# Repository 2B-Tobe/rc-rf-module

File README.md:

# RC RF Module

A 2.4 GHz multi-protocol RC transmitter module and receiver on one board, built around the EFR32MG24
(RF-BM-MG24B2I module), with an optional second radio — an SX1278 (RA-01) — that carries the same channels
on 459 MHz beside the 2.4 GHz link. One firmware serves both roles and both board variants.

| | |
|---|---|
| **Transmitter module** | takes the channels from a transmitter's encoder — PPM, or Multiprotocol serial frames — and sends them on nRF24, RLINK, FrSky D8, FrSky D16 (ACCST v1/v2, EU-LBT or FCC) or DSMX, with the 459 MHz link beside it when the RA-01 is fitted |
| **Receiver** | 8 servo outputs, PPM and SBUS; with the RA-01 fitted it listens on both bands and takes the servos from 459 MHz when 2.4 GHz goes quiet |
| **Setup** | protocol jumpers, or a setup stored in the module: written over its serial pins with the hand-held **Controller** (this repository) or a terminal |
| **Links of its own** | RLINK (two-way 2.4 GHz with telemetry, adaptive channels and power, alarms), nRF24 (the original 11 ms link), UK 459 MHz (10-byte hopping link) |

## Two board variants, one firmware

- **2.4 GHz only** — the RA-01 and its parts are left off. The firmware notices (`no SX1278 answered`) and runs
  2.4 GHz only.
- **2.4 GHz + 459 MHz** — the RA-01 fitted. The firmware runs the 459 MHz link beside every transmitter
  mode (selectable Single / Dual) and the 459 MHz receiver beside every receiver mode.

The servo outputs are on the same pins for both variants (`firmware/servo_pins.h`).

## What is where

| Folder | |
|---|---|
| `firmware/` | the EFR32 project (Simplicity SDK 2026.6.1, RAIL), `build.ps1`, `cfg.ps1`, prebuilt hex files — see `firmware/README.md` |
| `controller/` | the RF Module Controller: an STM32F103C8 box with a 128×64 display that sets the module up over its serial pins — STM32CubeIDE project, manual |
| `hardware/rf_module/` | the module carrier board: KiCad project, Gerbers, BOM and placement files |
| `hardware/controller/` | the controller board: KiCad project, Gerbers, BOM and placement files |
| `docs/` | operating quick sheet, flashing with an ST-Link, the serial input and setup command reference, the RLINK description |
| `CREDITS.md` | people, projects and components this builds on, with their licences |

## Start here

1. **Build a board** — `hardware/rf_module/README.md` (what to order, what to leave off for the 2.4 GHz-only variant).
2. **Flash it** — with only an ST-Link: `docs/FLASHING_STLINK.md` (the prebuilt firmware and a setup file for each
   role, no USB-serial adapter needed); to build it yourself: `firmware/README.md`.
3. **Use it** — `docs/QUICK_SHEET_EFR32_Module.md`: connections, roles, modes, bind, failsafe, LEDs.
4. **Feed it** — `docs/SERIAL_INPUT.md`: what a transmitter has to send (PPM or the Multiprotocol serial frame),
   and the text commands any programmer can use to set the module up.
5. **Controller** — `controller/README.md` and `controller/docs/MANUAL.md` to build and use the setup box.

## Regulatory note

The 2.4 GHz side is built for EU use: DSMX at 22 ms only and 18 dBm, FrSky D16 EU-LBT (Sub 0/1) with listen-before-talk (the D16 FCC versions, Sub 2/3/5, are for receivers with FCC firmware and have none), RLINK
with a clear-channel check before every packet. The 459 MHz link uses the UK 458.5–459.5 MHz model-control
band at 100 mW; check what your country allows before fitting the RA-01.

## Licence

The firmware, the documentation and the hardware design files are released under the **GNU GPL v3** (see
`LICENSE`). The Controller (`controller/`) is under the **MIT licence** (`controller/LICENSE`). Third-party
components keep their own licences, listed in `CREDITS.md`. The Silicon Labs RAIL radio library (a binary under Zlib)
and two printf files under the Silicon Labs MSLA are **not** in this repository: they come with the Simplicity SDK,
and `build.ps1` copies them in. The firmware licence includes an additional permission to build it with that library (top of `LICENSE`).

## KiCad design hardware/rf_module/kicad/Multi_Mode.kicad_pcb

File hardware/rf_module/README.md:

# RF module carrier board (Multi_Mode)

Carrier for the RF-BM-MG24B2I (EFR32MG24) module with the header for the RA-01 (SX1278, 459 MHz) radio.
Both board variants are this one PCB:

| Variant | Fit | Leave off |
|---|---|---|
| 2.4 GHz only | everything except the RA-01 | the RA-01 and its reset capacitor |
| 2.4 GHz + 459 MHz | everything | — |

The firmware is the same for both; it detects the RA-01 at power-up.

## Files

| | |
|---|---|
| `Multi_Mode.pdf` | the schematic |
| `kicad/` | the KiCad project (KiCad 5 format: `.pro`, `.sch`, `.kicad_pcb`; KiCad 6 and later open and convert it). The EFR32 module's symbol comes from the project library `rf_star`; its footprint is embedded in the board file |
| `gerber/` | Gerber and drill files (4 layers), and the same as one zip for the board house |
| `bom/` | `Multi_Mode-top-pos.csv` — component placement, top side |

## Connections (EFR32 pins)

| Function | Pin |
|---|---|
| J3 serial: RX in / TX out, GND | PA06 / PA05 (3.3 V, 1 k in series on RX) |
| PPM in, and telemetry out (to the encoder, or EdgeTX bay pin 5) | PB01, through the Schottky diode D3 (see below) |
| BIND, RANGE, F/S (jumpers / buttons to GND) | PB00, PB02, PB03 |
| Protocol jumpers PC00, PC01, PC02 | to GND |
| LED_A, LED_B | PC04, PC05 |
| Buzzer (passive) | PD02 |
| Receiver servo outputs 1–8 | PA07 PB04 PD04 PD05 PA00 PA08 PA09 PB05 |
| Receiver PPM out, SBUS out | PC03 (270 Ω series), PA03 |
| Receiver battery sense (47 k / 10 k divider, 100 nF) | PA04 |
| RA-01: SCK, MISO, MOSI, NSS, RESET | PC06, PC07, PC08, PC09, PD03 (DIO pins unconnected) |
| SWD (flashing) | SWCLK, SWDIO, GND, 3.3 V |

Supply: 3.3 V LDO on board; mind its heat above ~8 V input with both radios sending.

## The PPM line and D3

PB01 started as a PPM input only. The Schottky diode D3 between the PPM connector and PB01 (net PPM_IN) suits
that: the outside can pull the line low, the module never drives it. Since then the same line also carries
telemetry **out** of the module, to the MiTo encoder and to bay pin 5 (S.Port) of an EdgeTX radio. D3 blocks that
direction, so the radio sees no status, no protocol list and no sensors (a black-and-white radio then cannot even
reach the MiTo protocol).

- **Boards built so far:** on a transmitter module, bridge D3 with a solder blob or a short wire. A receiver does
  not use this line and needs nothing.
- **Next revision:** a 1 k resistor in parallel with D3. PPM still comes in through the diode, telemetry goes out
  through the resistor, and no bridge is needed.

The line keeps its TVS diode either way. The MiTo encoder and EdgeTX radios drive it at 3.3 V; with a radio that
drives 5 V, the 1 k (rather than a plain bridge) also limits the current into the EFR32 pin.

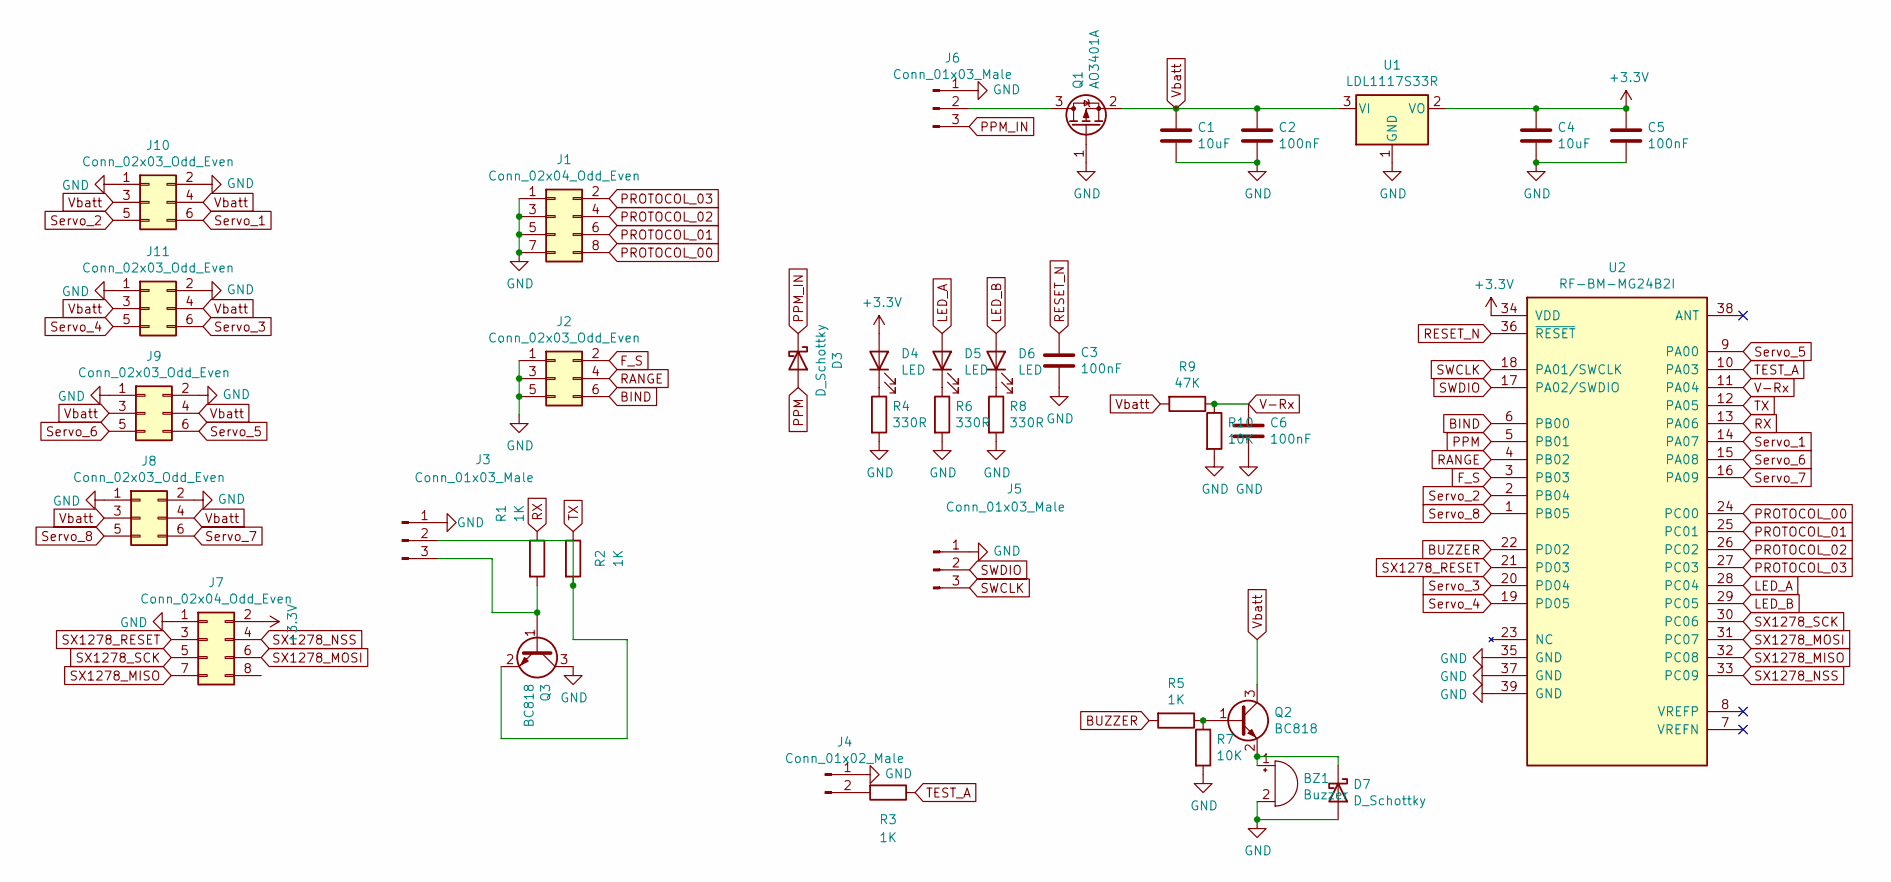
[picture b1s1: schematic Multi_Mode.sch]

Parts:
BZ1: Buzzer; CUI_CSS-0578-SMT
C1, C4: 10uF; C_0805_2012Metric
C2, C3, C5, C6: 100nF; C_0603_1608Metric
D3, D7: D_Schottky; D_SOD-323
D4, D5, D6: LED; LED_0603_1608Metric
J1, J7: Conn_02x04_Odd_Even; PinHeader_2x04_P2.54mm_Vertical
J2, J8, J9, J10, J11: Conn_02x03_Odd_Even; PinHeader_2x03_P2.54mm_Vertical
J3, J5, J6: Conn_01x03_Male; PinHeader_1x03_P2.54mm_Vertical
J4: Conn_01x02_Male; PinHeader_1x02_P2.54mm_Vertical
Q1: AO3401A; SOT-23
Q2, Q3: BC818; SOT-23
R1, R2, R3, R5: 1K; R_0603_1608Metric
R4, R6, R8: 330R; R_0603_1608Metric
R7, R10: 10K; R_0603_1608Metric
R9: 47K; R_0603_1608Metric
U1: LDL1117S33R; SOT-223-3_TabPin2
U2: RF-BM-MG24B2I

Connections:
+3V3: C4.1, C5.1, D4.2 (A), J7.2, U1.2 (VO), U2.34 (VDD)
BIND: J2.6, U2.6 (PB00)
BUZZER: R5.2, U2.22 (PD02)
F_S: J2.2, U2.3 (PB03)
GND: BZ1.2 (+), C1.2, C2.2, C3.2, C4.2, C5.2, C6.2, D7.2 (A), J1.1, J1.3, J1.5, J1.7, J2.1, J2.3, J2.5, J3.1, J4.1, J5.1, J6.1, J7.1, J8.1, J8.2, J9.1, J9.2, J10.1, J10.2, J11.1, J11.2, Q1.1 (G), Q3.3 (C), R4.2, R6.2, R7.2, R8.2, R10.2, U1.1 (GND), U2.35 (GND), U2.37 (GND), U2.39 (GND)
LED_A: D5.2 (A), U2.28 (PC04)
LED_B: D6.2 (A), U2.29 (PC05)
unnamed: BZ1.1 (-), D7.1 (K), Q2.2 (E)
unnamed: D4.1 (K), R4.1
unnamed: D5.1 (K), R6.1
unnamed: D6.1 (K), R8.1
unnamed: J3.2, Q3.2 (E), R2.2
unnamed: J3.3, Q3.1 (B), R1.2
unnamed: J4.2, R3.2
unnamed: J6.2, Q1.3 (D)
unnamed: Q2.1 (B), R5.1, R7.1
PPM: D3.2 (A), U2.5 (PB01)
PPM_IN: D3.1 (K), J6.3
PROTOCOL_00: J1.8, U2.24 (PC00)
PROTOCOL_01: J1.6, U2.25 (PC01)
PROTOCOL_02: J1.4, U2.26 (PC02)
PROTOCOL_03: J1.2, U2.27 (PC03)
RANGE: J2.4, U2.4 (PB02)
RESET_N: C3.1, U2.36 (~RESET)
RX: R1.1, U2.13 (PA06)
SWCLK: J5.3, U2.18 (PA01/SWCLK)
SWDIO: J5.2, U2.17 (PA02/SWDIO)
SX1278_MISO: J7.7, U2.32 (PC08)
SX1278_MOSI: J7.6, U2.31 (PC07)
SX1278_NSS: J7.4, U2.33 (PC09)
SX1278_RESET: J7.3, U2.21 (PD03)
SX1278_SCK: J7.5, U2.30 (PC06)
Servo_1: J10.6, U2.14 (PA07)
Servo_2: J10.5, U2.2 (PB04)
Servo_3: J11.6, U2.20 (PD04)
Servo_4: J11.5, U2.19 (PD05)
Servo_5: J9.6, U2.9 (PA00)
Servo_6: J9.5, U2.15 (PA08)
Servo_7: J8.6, U2.16 (PA09)
Servo_8: J8.5, U2.1 (PB05)
TEST_A: R3.1, U2.10 (PA03)
TX: R2.1, U2.12 (PA05)
V-Rx: C6.1, R9.1, R10.1, U2.11 (PA04)
Vbatt: C1.1, C2.1, J8.3, J8.4, J9.3, J9.4, J10.3, J10.4, J11.3, J11.4, Q1.2 (S), Q2.3 (C), R9.2, U1.3 (VI)

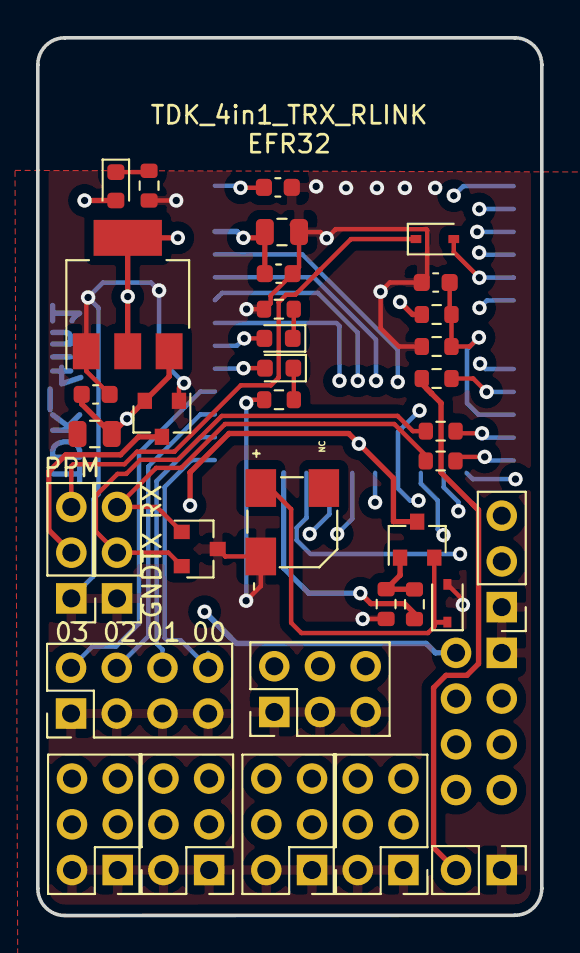
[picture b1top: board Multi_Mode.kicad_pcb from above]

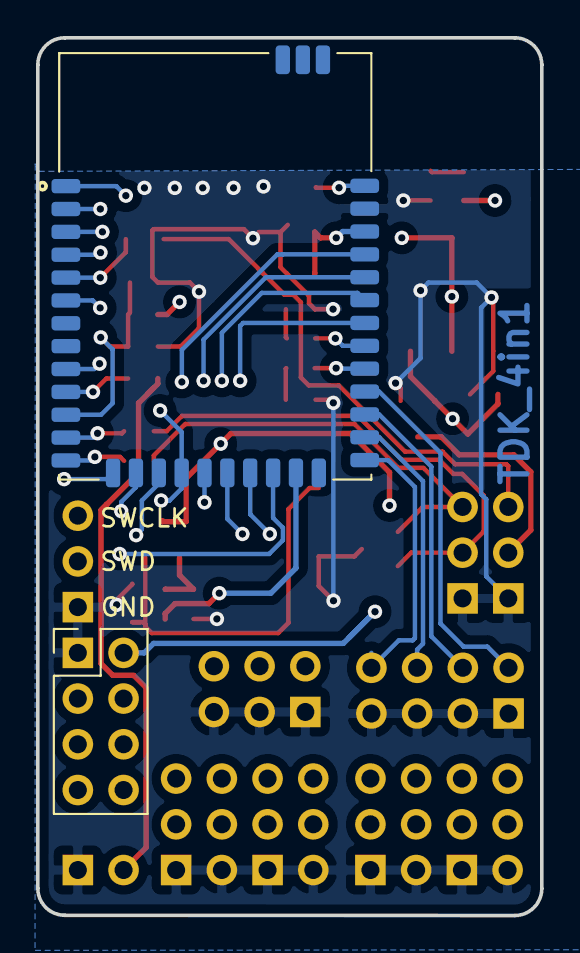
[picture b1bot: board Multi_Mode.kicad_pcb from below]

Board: 4 copper layers, 28.0 x 48.8 mm, 38 parts (2 on the bottom side), 44 nets.

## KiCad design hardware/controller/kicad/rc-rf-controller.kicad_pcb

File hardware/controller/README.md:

# Controller board (rc-rf-controller)

The hand-held box: STM32F103C8, a 128×64 UC1701 SPI display (JLX12864), five keys, buzzer, two 3-pin leads
to the module and an SWD header. Four-layer board.

## Files

| | |
|---|---|
| `rc-rf-controller.pdf` | the schematic |
| `kicad/` | the KiCad project (KiCad 5 format; KiCad 6 and later open and convert it). The tactile switch symbol is in the project library `rc-rf-controller-parts`; everything else is from KiCad's standard libraries; footprints are embedded in the board file |
| `gerber/` | Gerber and drill files, and the same as one zip for the board house |
| `bom/` | `rc-rf-controller-top-pos.csv` — component placement, top side |

## Connections (STM32 pins, see `controller/Core/Inc/board.h`)

| Function | Pin |
|---|---|
| Display SPI2: SCK, MOSI, CD/A0, RST, backlight | PB13, PB15, PB14, PB12, PB2 |
| Keys to GND: INC, DEC, BACK, ENTER, AUX | PB4, PA10, PB11, PB3, PB8 |
| To the module: J3 RX | PA9 (USART1 TX) |
| From the module: J3 TX | PA8 (software receiver; alternatives PA10, PA3 — `Core/Inc/serial.h`) |
| SWD | SWCLK PA14, SWDIO PA13, GND, 3.3 V |

Supply 3.3 V on board. The module's J3 pins are 3.3 V logic as well; GND common.

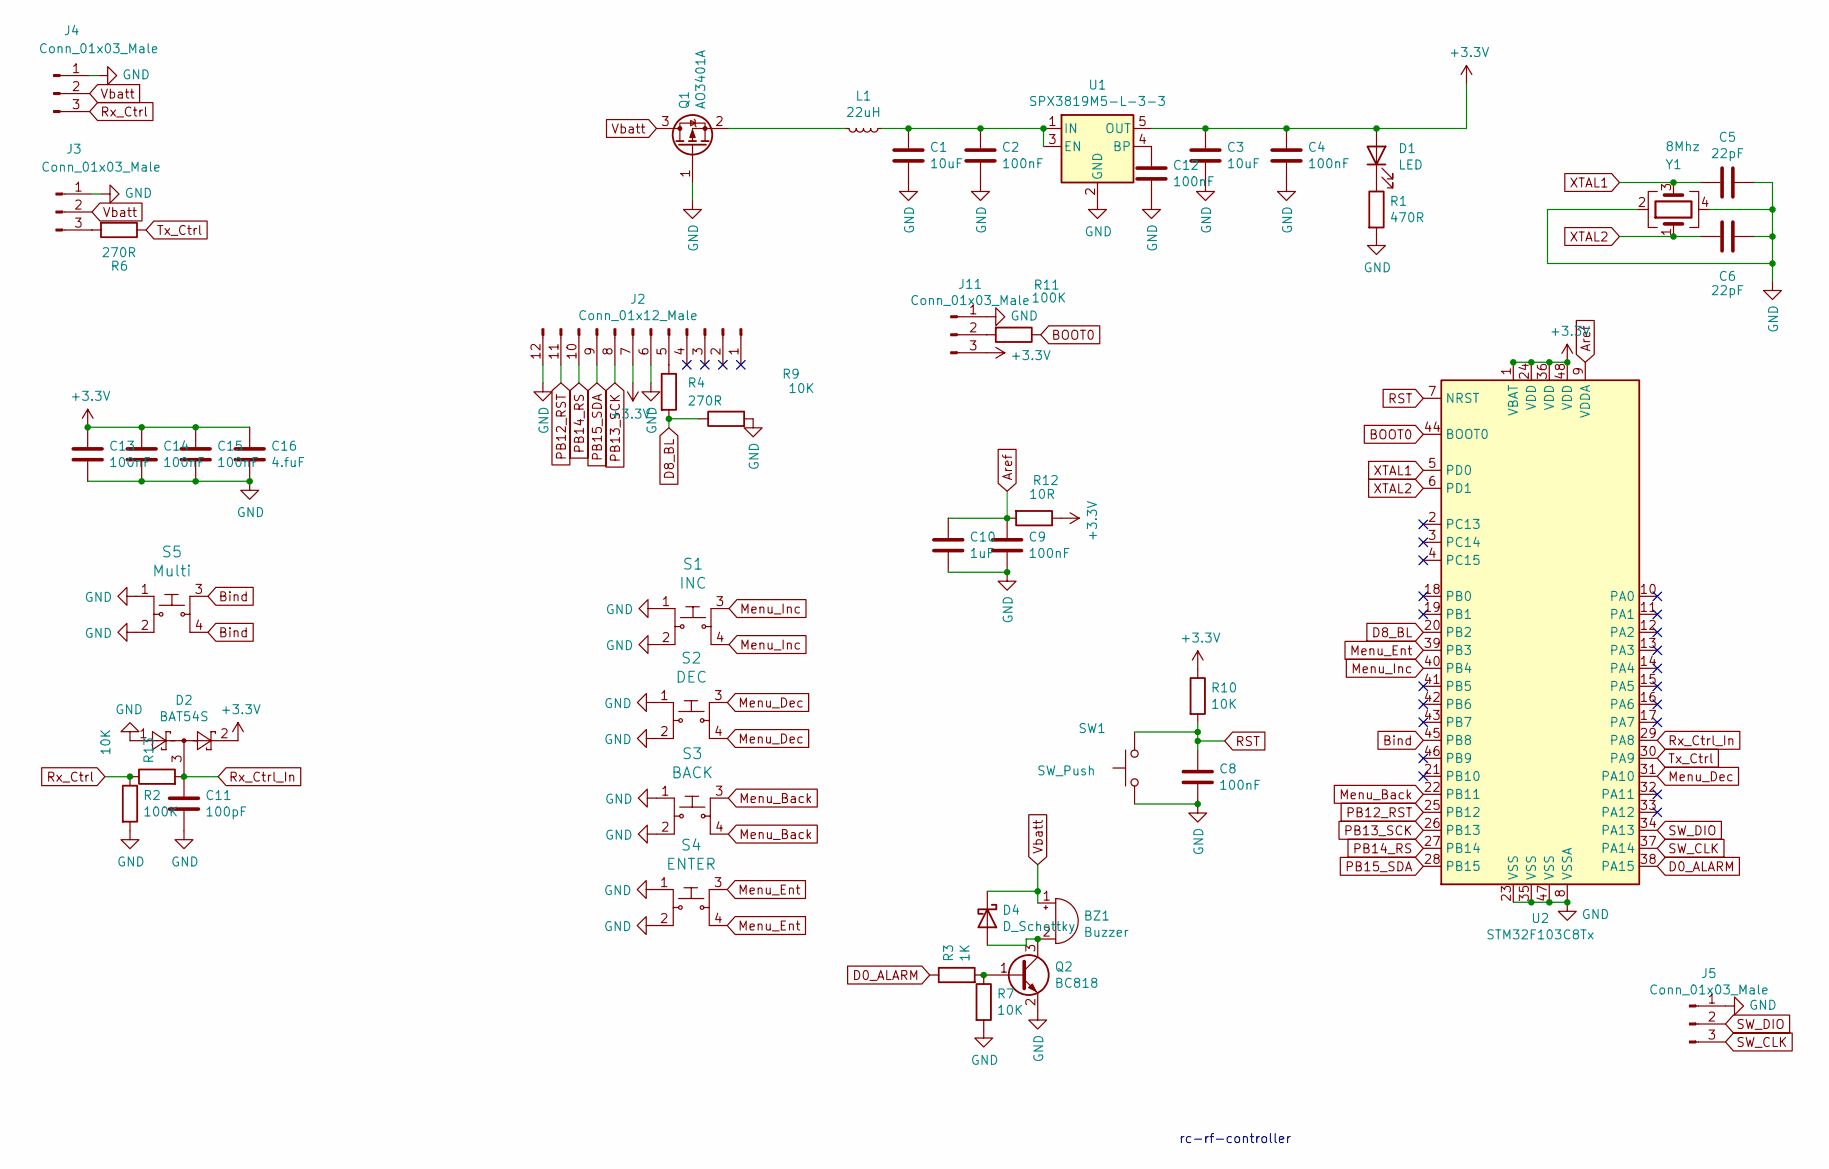
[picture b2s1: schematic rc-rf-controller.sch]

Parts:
BZ1: Buzzer; CUI_CSS-0578-SMT
C1, C3: 10uF; C_0805_2012Metric
C2, C4, C8, C9, C12, C13, C14, C15: 100nF; C_0603_1608Metric
C5, C6: 22pF; C_0603_1608Metric
C10: 1uF; C_0603_1608Metric
C11: 100pF; C_0603_1608Metric
C16: 4.fuF; C_0603_1608Metric
D1: LED; LED_0603_1608Metric
D2: BAT54S; SOT-23
D4: D_Schottky; D_SOD-323
J2: Conn_01x12_Male; PinHeader_1x12_P2.54mm_Vertical
J3, J4, J5: Conn_01x03_Male; PinHeader_1x03_P2.54mm_Vertical
J11: Conn_01x03_Male; SolderJumper-3_P1.3mm_Open_Pad1.0x1.5mm
L1: 22uH; Inductor_6060_MK
Q1: AO3401A; SOT-23
Q2: BC818; SOT-23
R1: 470R; R_0603_1608Metric
R2, R11: 100K; R_0603_1608Metric
R3: 1K; R_0603_1608Metric
R4, R6: 270R; R_0603_1608Metric
R7, R9, R10, R13: 10K; R_0603_1608Metric
R12: 10R; R_0603_1608Metric
S1: INC; SW_1825910-7; MPN 1825910-6; Digi-Key_PN 450-1650-ND
S2: DEC; SW_1825910-7; MPN 1825910-6; Digi-Key_PN 450-1650-ND
S3: BACK; SW_1825910-7; MPN 1825910-6; Digi-Key_PN 450-1650-ND
S4: ENTER; SW_1825910-7; MPN 1825910-6; Digi-Key_PN 450-1650-ND
S5: Multi; SW_1825910-7; MPN 1825910-6; Digi-Key_PN 450-1650-ND
SW1: SW_Push; SW_SPST_B3U-1000P
U1: SPX3819M5-L-3-3; SOT-23-5
U2: STM32F103C8Tx; LQFP-48_7x7mm_P0.5mm
Y1: 8Mhz; Crystal_SMD_3225-4Pin_3.2x2.5mm

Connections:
+3V3: C3.1, C4.1, C13.1, C14.1, C15.1, C16.1, D1.2 (A), D2.2, J2.7, J11.3, R10.1, R12.1, U1.5 (OUT), U2.1 (VBAT), U2.24 (VDD), U2.36 (VDD), U2.48 (VDD)
Aref: C9.1, C10.1, R12.2, U2.9 (VDDA)
BOOT0: R11.1, U2.44 (BOOT0)
Bind: S5.3, S5.4, U2.45 (PB8)
D0_ALARM: R3.1, U2.38 (PA15)
D8_BL: R4.2, R9.1, U2.20 (PB2)
GND: C1.2, C2.2, C3.2, C4.2, C5.1, C6.1, C8.2, C9.2, C10.2, C11.2, C12.2, C13.2, C14.2, C15.2, C16.2, D2.1, J2.6, J2.12, J3.1, J4.1, J5.1, J11.1, Q1.1 (G), Q2.2 (E), R1.2, R2.2, R7.2, R9.2, S1.1, S1.2, S2.1, S2.2, S3.1, S3.2, S4.1, S4.2, S5.1, S5.2, SW1.1, U1.2 (GND), U2.8 (VSSA), U2.23 (VSS), U2.35 (VSS), U2.47 (VSS), Y1.2, Y1.4
Menu_Back: S3.3, S3.4, U2.22 (PB11)
Menu_Dec: S2.3, S2.4, U2.31 (PA10)
Menu_Ent: S4.3, S4.4, U2.39 (PB3)
Menu_Inc: S1.3, S1.4, U2.40 (PB4)
unnamed: BZ1.2 (+), D4.2 (A), Q2.3 (C)
unnamed: C1.1, C2.1, L1.1, U1.1 (IN), U1.3 (EN)
unnamed: C12.1, U1.4 (BP)
unnamed: D1.1 (K), R1.1
unnamed: J2.5, R4.1
unnamed: J3.3, R6.2
unnamed: J11.2, R11.2
unnamed: L1.2, Q1.2 (S)
unnamed: Q2.1 (B), R3.2, R7.1
PB12_RST: J2.11, U2.25 (PB12)
PB13_SCK: J2.8, U2.26 (PB13)
PB14_RS: J2.10, U2.27 (PB14)
PB15_SDA: J2.9, U2.28 (PB15)
RST: C8.1, R10.2, SW1.2, U2.7 (NRST)
Rx_Ctrl: J4.3, R2.1, R13.1
Rx_Ctrl_In: C11.1, D2.3, R13.2, U2.29 (PA8)
SW_CLK: J5.3, U2.37 (PA14)
SW_DIO: J5.2, U2.34 (PA13)
Tx_Ctrl: R6.1, U2.30 (PA9)
Vbatt: BZ1.1 (-), D4.1 (K), J3.2, J4.2, Q1.3 (D)
XTAL1: C5.2, U2.5 (PD0), Y1.3
XTAL2: C6.2, U2.6 (PD1), Y1.1

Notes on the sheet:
rc-rf-controller

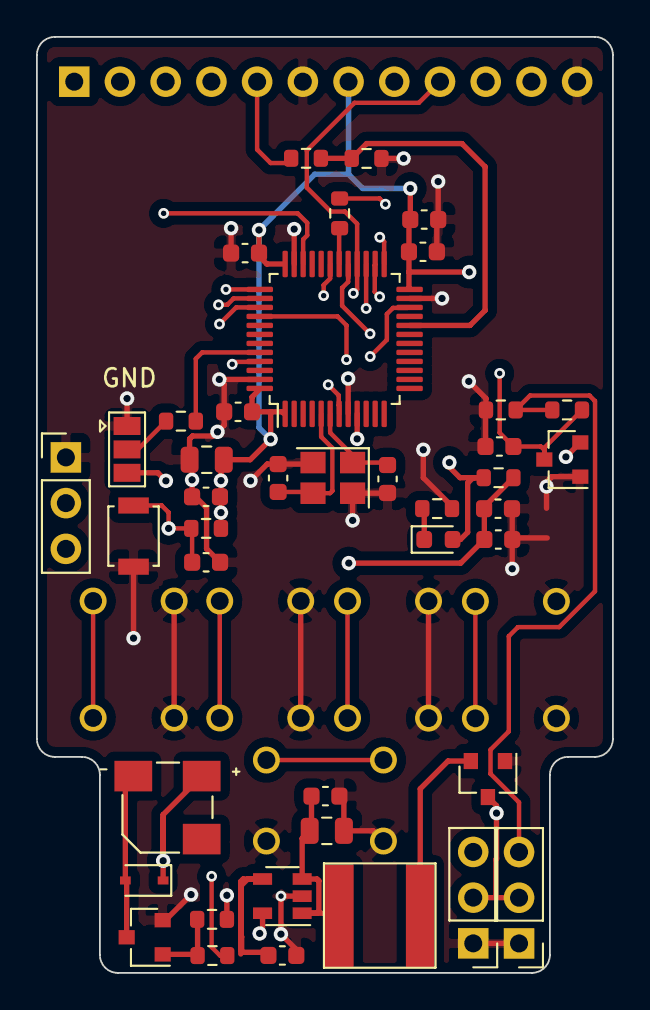
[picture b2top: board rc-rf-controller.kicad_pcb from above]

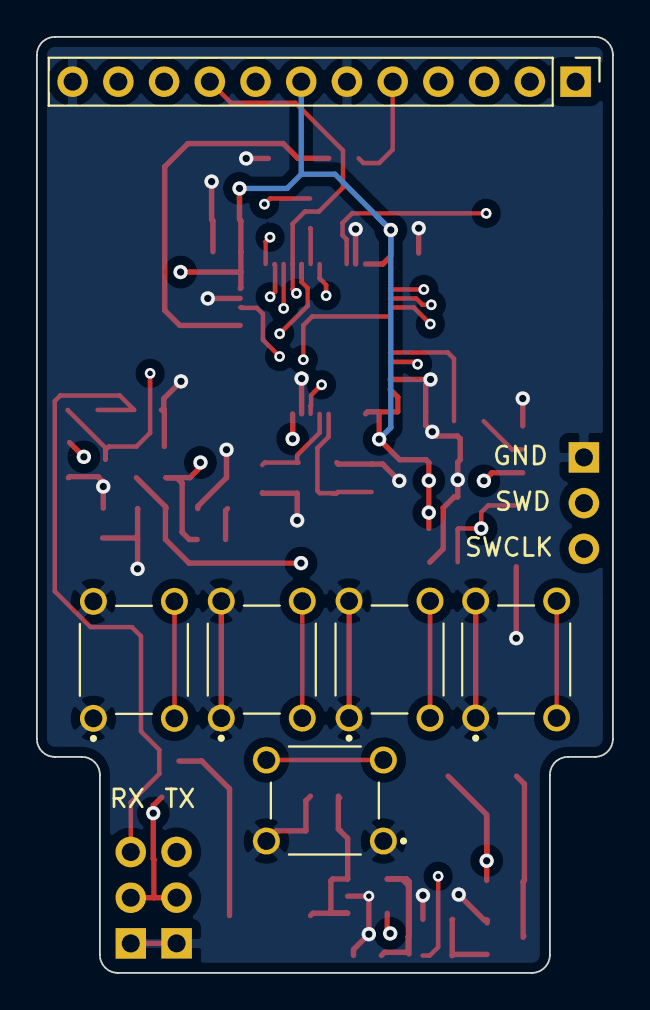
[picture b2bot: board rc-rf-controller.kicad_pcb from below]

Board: 4 copper layers, 32.0 x 52.0 mm, 47 parts (6 on the bottom side), 33 nets.

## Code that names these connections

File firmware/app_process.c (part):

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 *  - 11 ms frames, cadence: PRIMARY, PRIMARY, AUX
 *  - startup bind: ALWAYS first 1500 ms on BIND_PIPE, hop[0], PA min;
 *    bind button held keeps binding; release after hold -> system reset
 *  - failsafeFlag = F_S input (PB03, active low). PPM loss -> channels 1400 us.
 *  - RANGE input (PB02, active low) -> PA min in flight (range check)
 * Inputs: PPM PB01 (falling edges), BIND PB00 (simple_button), RANGE PB02, F_S PB03
 * SERIAL CONTROL (bay_serial.c): only a transmitter (F/S open) with the RANGE jumper fitted at power-up.
 *   Then the transmitter controls the module through its MULTI frames on PA06 (J3 RX)
 *   and overrides every other jumper: the frames' Prot / Sub choose the protocol, the frames carry the channels, BIND
 *   and RANGE (the BIND pin still works beside them; the RANGE pin is the "encoder" jumper here, not range check).
 *     Prot 3 = FrSky D8, 15 = FrSky D16 (Sub 0 v1 EU-LBT, 1 v2 EU-LBT, 2 v1 FCC, 3 v2 FCC, 5 v1 FCC 8 ch), 6 Sub 2 / 3 = DSMX 22 / 11 ms (11 ms only with DTX_EU_LOCK 0),
 *     0 Sub 0 = nRF24, 0 Sub 1 = RLINK, 0 Sub 7 = TX test; anything else: RF off, both LEDs blink, the log says why.
 *   The module waits for the first frames (both LEDs blink together) and restarts by itself when Prot / Sub
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 *   No frames later: input lost, as without PPM.
 *   Every other jumper setting -- no RANGE jumper, or F/S fitted -- works exactly as before.
 *   A stored TX setup ("cfg tx", or the controller box) does the same with no jumpers at all: F/S open, the
 *   module waits for MULTI frames on PA06 or PPM on PB01 and the first to bring 3 frames wins until the next
 *   power-up -- MULTI = encoder control as above, PPM = the stored protocol and Opt. F/S fitted = MULTI only.
 * DUAL build (branch dual-serial): an SX1278 (RA-01) on PC06-PC09 + PD03 carries Tobe's UK 459 MHz link
 *   (uk459_tx.c) beside every transmitter role -- the same channels, BIND and RANGE as the 2.4 GHz side, from PPM or
 *   from the encoder's frames; with RLINK only while RLINK's link alarm is on --; it sleeps in DSM capture, TX test
 *   and, for now, the receiver roles. With the encoder the UK ID includes the Rx No too (per-model binding; Rx No 0 =
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#include "sbus_out.c"
#include "nrf24_rx.c"
#include "dsm_cap.c"
#include "jeti_cap.c"   // Jeti Duplex sniffer: 802.15.4 frames on channels 11..26 -> UART (PC00 + PC02, or encoder Prot 0 Sub 6)
#include "dsm_rx.c"
// EU build: DSMX 22 ms only (dsm_tx.c v1.14). Set 0 for use outside the EU, where 11 ms is allowed.
#define DTX_EU_LOCK 1
#include "dsm_tx.c"
#include "tx_test.c"
#include "bay_serial.c" // encoder MULTI frames on PA06 (EUSART1 RX): protocol, channels, BIND, RANGE
#include "etx_multi.c"  // ... or an EdgeTX radio's (inverted): the module answers as a Multiprotocol module
#include "uk459_tx.c"   // second radio: SX1276/78, UK 459 MHz link beside the 2.4 GHz transmitter roles
#include "uk459_rx.c"   // ... and the 459 MHz receiver role (PC01 + PC02 + F/S): V7 ported

// FrSky D8 / D16 power, same convention as nRF24 / RLINK / DSMX: flight at the module maximum (200 = +20 dBm
// requested; RAIL caps it at what the PA delivers), bind & RANGE -10 dBm.
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#define PKT_AUX      2

#define TX_POWER_MAX_DDBM   200    // flight: module maximum (+20 dBm requested, RAIL caps it); was 0 = nRF24 PA_MAX parity
#define TX_POWER_MIN_DDBM  -100    // -10.0 dBm ("PA_MIN": bind & range check)

/// nRF24 air order: address MSByte-first, MSbit-first. EFR32 sync register
/// transmits least-significant BIT first => load addr[0]..addr[3] MSB->LSB
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#define ADDR_BYTE_REVERSE  0
#define ADDR_BIT_REVERSE   1

/// 1 = read BIND (PB00, active low) to extend/force bind; 0 = bind only via the
/// 1.5 s boot window (the proven-working bench state; set 1 once PB00 hardware
/// is verified: 3.3 V idle, 0 V when shorted to its GND pin).
#define BIND_PIN_ENABLED   0

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static volatile uint64_t radio_events = 0;
static volatile sl_rail_status_t calibration_status = 0;

// PPM (updated in GPIO IRQ) — verbatim semantics from the AVR ICP1 ISR
static volatile uint16_t contrl_pos[8] = {1500,1500,1500,1500,1500,1500,1500,1500};
static volatile uint16_t scaled10[5];
static volatile uint8_t  scaled8[3];
static volatile uint8_t  ppmCounter = 0;
static volatile uint32_t ppm_last_edge = 0;
static volatile uint32_t ppm_last_sync = 0;   // for loss detection
static volatile uint32_t ppm_syncs = 0;       // sync gaps seen, total (bay_detect: PPM or MULTI, whichever comes first)
// PPM diagnostic: same glitch seen in nRF24 mode too, so look at the encoder's own PPM signal,
// independent of which RF protocol is running. Printed once a second from app_process_action().
static uint16_t          ppm_prev_frame[8] = {1500,1500,1500,1500,1500,1500,1500,1500};
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#define PPM_DIAG 1
#endif

static sl_gpio_t range_pin = { .port = SL_GPIO_PORT_B, .pin = 2 }; // RANGE, act.low
static sl_gpio_t fs_pin    = { .port = SL_GPIO_PORT_B, .pin = 3 }; // F_S,   act.low
static sl_gpio_t bind_pin  = { .port = SL_GPIO_PORT_B, .pin = 0 }; // BIND,  act.low
static sl_gpio_t led_a     = { .port = SL_GPIO_PORT_C, .pin = 4 }; // LED_A: TX activity
static sl_gpio_t led_b     = { .port = SL_GPIO_PORT_C, .pin = 5 }; // LED_B: PPM activity
static sl_gpio_t proto0_pin = { .port = SL_GPIO_PORT_C, .pin = 0 }; // PROTOCOL_00, act.low
static sl_gpio_t proto1_pin = { .port = SL_GPIO_PORT_C, .pin = 1 }; // PROTOCOL_01, act.low
static sl_gpio_t proto2_pin = { .port = SL_GPIO_PORT_C, .pin = 2 }; // PROTOCOL_02, act.low
// Protocol select at boot: all floating -> nRF24 (+ F/S low = nRF24 receiver); PC02 low -> RLINK (PC01 ignored);
// PC00 low -> FrSky D8; PC01 low -> FrSky D16 (v1 EU-LBT)
typedef enum { PROTO_NRF24 = 0, PROTO_D8, PROTO_D16, PROTO_RLINK, PROTO_DSMCAP, PROTO_DSMRX, PROTO_DSMTX, PROTO_TXTEST, PROTO_JETICAP, PROTO_UKONLY, PROTO_UKRX } proto_t;
static proto_t proto = PROTO_NRF24;
static bool    nrf_rx_role = false;      // nRF24 + F/S low at boot: receiver role (nrf24_rx.c)
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#define alt_mode (proto != PROTO_NRF24)

// Encoder serial control (bay_serial.c)
static bool          bay_listen      = false;   // transmitter role: EUSART1 listens on PA06
static volatile bool bay_mode        = false;   // MULTI frames at power-up: the encoder chose the role and feeds it
static bool          bay_unsupported = false;   // ... but asked for a Prot / Sub this module does not have: RF off
static bool          bay_bind_now    = false;   // BIND on in the frames
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
// Direct-GPIO LEDs: the SDK's toggle_send_led() is a NO-OP unless the LED
// instance is named "led0" (SL_CATALOG_LED0_PRESENT) — ours is inst0.
static inline void led_a_toggle(void) { sl_gpio_toggle_pin(&led_a); }
static inline void led_b_toggle(void) { sl_gpio_toggle_pin(&led_b); }

static void start_frame_timer(void);

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}

// -------------------------------------------------------------- PPM capture -
// The pulse edges are timestamped by TIMER0 CC0 hardware capture (PB01 -> EXTI -> PRS ch 7 ->
// TIMER0 CC0, 1 MHz ticks): the time latches in silicon at the edge, like the AVR's ICP1, so
// interrupt latency cannot touch the measurement. Software ISR timestamps showed 65-99 us of
// jitter with the sticks held still, in every RF mode; raising the GPIO interrupt priority
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
static void inputs_init(void)
{
  sl_gpio_t ppm_pin = { .port = SL_GPIO_PORT_B, .pin = 1 };      // PB01
  sl_gpio_set_pin_mode(&ppm_pin, SL_GPIO_MODE_INPUT_PULL, 1);
  int32_t int_no = SL_GPIO_INTERRUPT_UNAVAILABLE;
  sl_gpio_configure_external_interrupt(&ppm_pin, &int_no,
                                       SL_GPIO_INTERRUPT_FALLING_EDGE,
                                       (sl_gpio_irq_callback_t)ppm_edge_cb, NULL);
  // Hardware timestamping (see ppm_capture above). The call above routed PB01 to EXTI line
  // int_no; that same routing feeds the pin level to PRS. The software edge interrupt is
  // turned off -- TIMER0 CC0 latches each falling edge in hardware and its ISR reads the
  // captured time, so no interrupt latency or critical section can jitter the pulse widths.
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    NVIC_EnableIRQ(TIMER0_IRQn);
    TIMER_Enable(TIMER0, true);
  }
  sl_gpio_set_pin_mode(&range_pin, SL_GPIO_MODE_INPUT_PULL, 1);  // pull-ups
  sl_gpio_set_pin_mode(&fs_pin,    SL_GPIO_MODE_INPUT_PULL, 1);
  sl_gpio_set_pin_mode(&bind_pin,  SL_GPIO_MODE_INPUT_PULL, 1);
  sl_gpio_set_pin_mode(&led_a,     SL_GPIO_MODE_PUSH_PULL, 0);   // LEDs
  sl_gpio_set_pin_mode(&led_b,     SL_GPIO_MODE_PUSH_PULL, 0);
}

static bool pin_low(const sl_gpio_t *p)
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  return !v;
}

// BIND / RANGE of the transmitter roles: the pins, or BIND / RANGE in the serial frames
static uint32_t cfg_bind_until = 0;             // "cfg bind": BIND counts as held until this RAIL time (0 = no)
static bool bind_held(void)                     // the BIND jumper, or the virtual one after "cfg bind"
{
  if (pin_low(&bind_pin)) return true;
  if (cfg_bind_until != 0u) {
    uint32_t now = (uint32_t)sl_rail_get_time(sl_rail_util_get_handle(SL_RAIL_UTIL_HANDLE_INST0));
    if ((int32_t)(now - cfg_bind_until) < 0) return true;
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
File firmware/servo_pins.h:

/*
 * servo_pins.h — servo outputs 1..8 of every receiver role, DUAL build (branch dual-serial).
 *
 * The dual build has the SX1278 (RA-01) on PC06 PC07 PC08 PC09 and PD03, the pins the single build uses for
 * servos 2 and 5..8. Here those five servos move to module pads the Multi_Mode carrier leaves unconnected;
 * servos 1, 3 and 4 stay where they were. A receiver board for the dual build must route these to its header.
 *
 *   servo   1     2     3     4     5     6     7     8
 *   pin     PA07  PB04  PD04  PD05  PA00  PA08  PA09  PB05
 *   module  14    2     20    19    9     15    16    1
 *
 * PB04 is the SX1278's DIO0 on the schematic; the dual build does not use DIO0 (it reads the SX1278 over SPI).
 * Unchanged: PPM PC03, SBUS PA03, RLINK battery sense PA04.
 */
#ifndef SERVO_PINS_H
#define SERVO_PINS_H
#include "sl_gpio.h"

#define SERVO_PINS_INIT { \
  { .port = SL_GPIO_PORT_A, .pin = 7 }, { .port = SL_GPIO_PORT_B, .pin = 4 }, \
  { .port = SL_GPIO_PORT_D, .pin = 4 }, { .port = SL_GPIO_PORT_D, .pin = 5 }, \
  { .port = SL_GPIO_PORT_A, .pin = 0 }, { .port = SL_GPIO_PORT_A, .pin = 8 }, \
  { .port = SL_GPIO_PORT_A, .pin = 9 }, { .port = SL_GPIO_PORT_B, .pin = 5 } }

#endif /* SERVO_PINS_H */

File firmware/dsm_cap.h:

/*
 * dsm_cap.h — DSM (Spektrum / CYRF6936) raw chip capture role for the EFR32MG24 module.  v3.29
 *
 * Not a receiver: it finds the channel a DSM transmitter is on with an RSSI sweep, centres
 * on the carrier in 125 kHz steps, then alternates two ways of recording the 1 Mchip/s DSSS
 * signal and prints the captures as hex on the bay UART (PuTTY log = the capture,
 * dsm_analyse.py decodes):
 *   packet phase  dsm_raw PHY in packet mode, fixed 1024-byte frames = 8192 hard chips per
 *                 frame if the modem's timing detector locks on the CYRF preamble ("DCP")
 *   soft phase    RAIL demod-data source: 8-bit soft samples (6 MS/s), free-running 4096-sample
 *                 snapshots, the two strongest printed ("DCS"), from the lock and from +-125 kHz
 * Channels in the log are MHz channels with a fraction: "38.5" = 2438.5 MHz (f= gives kHz).
 * Purpose: learn the exact DSM air format from a real transmitter before writing an
 * EFR32 DSM receiver/transmitter.
 *
 * Boot jumpers:  PROTOCOL_00 + PROTOCOL_01 + PROTOCOL_02 (PC00 + PC01 + PC02) fitted (PC00 + PC01 alone is the DSMX transmitter, + F/S the receiver).
 *   (v3.29: PC02 selects the role, so the carrier-detect output is LED_A only)
 *   PC03 (J1 PROTOCOL_03)  DOUT: modem DOUT via PRS (experimental, DC_PRS_DOUT)
 *   PA03 (J4 TEST_A)       DCLK: modem DCLK via PRS (experimental, DC_PRS_DOUT)
 *   LED_A = CD, LED_B: toggles once per hunt sweep, steady when locked
 *   BIND fitted at boot -> bind sniffer: fixed on 2414 MHz, DCK/DCD cycle (v3.31); BIND while hunting -> drop the lock
 *   RANGE low at boot -> data test: census, then frames on the busiest channel (v3.27)
 *   F/S low at boot -> the DSMX receiver role instead (dsm_rx.c); the any-burst hunt option is gone
 *   UART PA05 115200: "DC hunt", "DC sweep ...", "DC lock ch=..", "DC phase packet|soft",
 *                     "DC peak ch=..: .. dBm, mid .., sat ..%, modulation ..%"   (1 MHz, then 125 kHz steps)
 *                     "DC P ch=.. r=.. d=..% b=.. max=.. tim=.. pre=.. sync=.. pkt=.."  1x/s
 *                     "DC S ch=.. r=.. b=.. snaps=.. strongest=.."                     1x/s
 *                     "DCK ch=.. rssi=.. sync=.. sel=.. order=.. inv=.. q=../32 bytes=<16 bytes> sum1=OK sum2=OK"  (v3.20:
 *                     a frame received by the modem and despread; needs the 0011-preamble PHY)
 *                     "DCP ch=.. f=.. rssi=.. sync=.. len=1020" + hex + "DCE"   (packet phase frames)
 *                     "DCX ch=.. rssi=.. sop=.. q=../64 crc=OK bytes=<19 bytes> | ch1=1244 ..."  (v3.28: a DSMX
 *                     data packet decoded in the firmware, data test, 5/s at most)
 *                     "DCT ch=.. n=.. t0=..: 125010/A1/-24 127990/B2/-24 ..."  (v3.28: every frame of the last
 *                     second: microseconds since the previous frame / kind / RSSI; kind A = upper frame
 *                     (channels 0 7 3 8 9 11), B = lower frame (1 5 2 4 6 10), then 1 or 2 = first or
 *                     second packet of the 4 ms pair (by CRC seed); x = CRC failed, n = no SOP)
 *                     "DCS ch=.. f=.. rssi=.. len=4096 sat=.. tr=.. mid=.. fs=.." + hex + "DCE"
 *                     "DCW ..." same, a pinned snapshot (mid = p10/p90 midpoint of the samples)
 *                     snapshots are the two taken at the highest RSSI in the phase (v3.16)
 *                     "DCD ch=.. f=.. rssi=.. len=32768 dec=2 pre=3072 fs=.. ovf=.." + hex + "DCE"  (v3.19:
 *                     one triggered burst, 1 ms before the RSSI edge and 9.6 ms after, every 2nd
 *                     sample = 3 per chip; dsm_analyse.py recovers the chip timing and the bytes)
 *
 * Over SWD: dsm_cap_diag[] (int32) and dsm_cap_peak[126] (int8 dBm, all-time max per channel)
 */
#ifndef DSM_CAP_H
#define DSM_CAP_H
#include <stdint.h>
#include <stdbool.h>
#include "sl_rail.h"

void dsm_cap_start(sl_rail_handle_t rh, bool fixed, bool any_burst);   /* fixed = RANGE low, any_burst = F/S low */
void dsm_cap_service(bool bind_held);     /* every main-loop pass */
void dsm_cap_rx_process(void);            /* a packet is held in RAIL (packet phase frames)          */
void dsm_cap_on_events(sl_rail_events_t events);   /* from the RAIL event callback (ISR) */

#define DC_CHANNELS 126u
#define DC_DIAG_N   24u
extern volatile int32_t dsm_cap_diag[DC_DIAG_N];
extern volatile int8_t  dsm_cap_peak[DC_CHANNELS];   /* all-time max RSSI per channel, dBm  */
extern volatile int8_t  dsm_cap_scan[DC_CHANNELS];   /* max RSSI per channel, last sweep    */
#define DC_STATE     0   /* 0 init, 1 hunt, 2 confirm, 3 locked, 4 peak search           */
#define DC_SUPPORT   1   /* sl_rail_supports_rx_raw_data()                                 */
#define DC_CFG_ERR   2   /* 1 chans 2 rx-data-config 4 fifo 8 start-rx 16 fixed-length    */
#define DC_CH        3   /* quarter channel the radio is on (2400 + n/4 MHz)               */
#define DC_LOCK_RSSI 4   /* RSSI that produced the lock, dBm                               */
#define DC_RSSI      5   /* latest RSSI reading, dBm                                       */
#define DC_BURSTS    6   /* carrier-detect rising edges while locked                       */
#define DC_SWEEPS    7   /* hunt sweeps completed                                          */
#define DC_BEST_CH   8   /* best channel of the last sweep                                 */
#define DC_BEST_RSSI 9   /* its RSSI, dBm                                                  */
#define DC_2ND_CH   10   /* runner-up channel of the last sweep                            */
#define DC_2ND_RSSI 11   /* its RSSI, dBm                                                  */
#define DC_FLOOR    12   /* lowest channel maximum of the last sweep (noise floor), dBm    */
#define DC_INVALID  13   /* RSSI reads that returned SL_RAIL_RSSI_INVALID                  */
#define DC_DUTY     14   /* carrier-detect duty over the last status period, percent       */
#define DC_RELOCKS  15   /* times the lock was dropped (silence or BIND)                   */
#define DC_CD       16   /* carrier-detect output right now                                */
#define DC_THRESH   17   /* detect threshold in use, dBm                                   */
#define DC_FIFO_SZ  18   /* RX FIFO size RAIL granted, bytes                               */
#define DC_OVERFLOW 19   /* RX FIFO overflows (each soft snapshot ends with one)           */
#define DC_CAPTURED 20   /* burst captures completed (v3.18)                               */
#define DC_SENT     21   /* captures printed on the UART                                   */
#define DC_READS    22   /* RSSI reads total (loop rate check)                             */
#define DC_LONGEST  23   /* longest carrier-detect burst seen, microseconds                */
#endif

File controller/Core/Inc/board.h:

/*
 * board.h - the controller board: STM32F103C8 (72 MHz from an 8 MHz crystal), a 128x64 UC1701 display on SPI2,
 * four menu keys and one extra key, and the serial link to the RF module.
 *
 *   Display   SPI2: SCK PB13, MOSI PB15, CD (A0) PB14, RST PB12, no CS; backlight PB2
 *   Keys      INC PB4, DEC PA10, BACK PB11, ENTER PB3, AUX PB8 (all to GND, internal pull-ups; JTAG disabled, SWD kept)
 *   Link      TX: USART1 PA9, 115200 8N1  -> module J3 RX
 *             RX: see LINK_RX_PIN in serial.h <- module J3 TX
 *
 * Everything is register level (CMSIS device header only), no HAL.
 */
#ifndef BOARD_H
#define BOARD_H
#include <stdint.h>
#include <stdbool.h>

#define KEY_INC   0x01u
#define KEY_DEC   0x02u
#define KEY_BACK  0x04u
#define KEY_ENTER 0x08u
#define KEY_AUX   0x10u

void     board_init(void);            /* clocks, SysTick (1 ms), pins */
uint32_t board_ms(void);              /* milliseconds since start */
void     board_delay_ms(uint32_t ms);
void     board_delay_us(uint32_t us);
uint8_t  board_keys(void);            /* KEY_* bits, 1 = pressed (raw, not debounced) */
void     board_backlight(bool on);

/* display lines, used by display.c */
void     board_spi_write(uint8_t b);
void     board_disp_cd(bool data);    /* false = command, true = data */
void     board_disp_reset(bool high);
#endif

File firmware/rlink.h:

/*
 * rlink.h — RLINK, resilient two-way 2.4 GHz RC link (EFR32MG24).
 * #included into app_process.c like the other protocols.
 * Specified in "RLINK Protocol Specification" and "RLINK System Specification".
 *
 * Boot jumpers:  PC02 low                = RLINK transmitter
 *                PC02 + F/S low          = RLINK receiver
 *                + BIND held on both     = private bind (RX first)
 *                TX + RANGE low          = range check, fixed -10 dBm
 *                RX + RANGE low          = bench test: RX ignores copy A on RF 12..20
 *   TX outputs:  PD02 buzzer beeps alarms; PA07 high = alarm (for the encoder);
 *                bay UART PA05 115200: "RL q.. a.. b.. u.. p.. m.. s.. i.. l.. v.." ~5.7x/s
 *                beeps: 2 = weak link, 3 = RX battery low, continuous = land now
 *                (RX battery 4-cell/5 V: 4.6 / 4.4 V, 2S LiPo: 7.2 / 6.8 V, picked from the first reading)
 *   Every transmission uses listen-before-talk: busy channel -> packet skipped.
 *   RX outputs:  PPM PC03, 8 servo pulses (servo_pins.h), SBUS on PA03 (100 kbaud 8E2, inverted)
 *   RX input:    battery on PA04 via 47k/10k divider from Vbatt (none fitted -> no sensor)
 *   RX:          failsafe preset = hold BIND 0.3 s while linked
 */
#ifndef RLINK_H
#define RLINK_H
#include <stdint.h>
#include <stdbool.h>
#include "sl_rail.h"

void rlink_start(sl_rail_handle_t rh, const volatile uint16_t *ch_us, bool rx_role, bool range_low, bool bind_held);
void rlink_action(void);
void rlink_on_events(sl_rail_events_t events);
void rlink_rx_process(void);
void rlink_input(bool ok);   /* TX: call every loop with "encoder PPM present" */
void rlink_range(bool low);  /* TX: call every loop with the RANGE input (low = -10 dBm range check) */
void rlink_bind(bool held);  /* TX: call every loop; true (BIND on in the serial frames) keeps the bind going.
                                The bind at power-up lasts RL_BIND_MS (1.5 s) at least, and then as long as this
                                stays true. Jumper mode passes false: 1.5 s, as before. */

/* TX, for the encoder's telemetry: microseconds since the last telemetry packet from the receiver, and whether
   one has been heard at all since this role started. */
uint32_t rlink_tele_age_us(uint32_t now);
bool     rlink_ever_linked(void);

#define RL_DIAG_N 58u
extern volatile int32_t rlink_diag[RL_DIAG_N];
#define R_ROLE   0
#define R_INLOST 1   /* TX: 1 = encoder PPM lost / RX: frames received flagged "TX input lost" */
#define R_SEQ    2
#define R_FTX    3
#define R_TXOK   4
#define R_TXER   5
#define R_BIND_SEEN 6
#define R_FRX    7
#define R_CRX    8
#define R_FLOST  9
#define R_CRCB  10
#define R_CH0   11
#define R_CH1   12
#define R_LQ    13
#define R_RSSI  14
#define R_WORST 15
#define R_GOT_A 16
#define R_SAVED_B 17
#define R_LATE  18
#define R_PWR   19
#define R_SYNC_NOW 20   /* sync word the radio is actually using right now        */
#define R_SYNC_ST  21   /* status of the last sync-word write (0 = OK)             */
#define R_SYNC_FIX 22   /* times the sync word had been reset and was re-applied   */
#define R_BIND_TX  23   /* TX: bind packets sent                                   */
#define R_STATE    24   /* bits: 1 rxbind, 2 acq, 4 saved bind, 8 provisional,
                           16 TX bind burst, 32 BIND pin reads low, 64 LBT refused (sent plain)                */
#define R_RSSI_B   25   /* RX: RSSI of the last copy-B packet, dBm ([14] = copy A)  */
/* R2 telemetry */
#define R_T_ASK    26   /* TX: telemetry windows opened / RX: telemetry replies sent */
#define R_T_GOT    27   /* TX: telemetry packets received                           */
#define R_T_LQ     28   /* TX: RX link quality, %                                   */
#define R_T_RSSIA  29   /* TX: RSSI at the RX, copy A, dBm                          */
#define R_T_RSSIB  30   /* TX: RSSI at the RX, copy B, dBm                          */
#define R_T_SAVEDB 31   /* TX: RX frames saved by copy B (16-bit, wraps)            */
#define R_T_LOST   32   /* TX: RX frames lost (16-bit, wraps)                       */
#define R_T_CRCB   33   /* TX: RX CRC errors (16-bit, wraps)                        */
#define R_T_FLAGS  34   /* TX: bit0 RX in failsafe, bit1 provisional, bits 8-15 worst dropout /10 ms */
#define R_T_RSSI_UP 35  /* TX: RSSI of the telemetry packet at the TX, dBm          */
/* R3a channel blacklisting (both roles) */
#define R_MAP_VER  36   /* active channel map version (0 = nothing blacklisted)     */
#define R_MAP_NA   37   /* blacklisted A channels                                   */
#define R_MAP_NB   38   /* blacklisted B channels                                   */
#define R_MAP_SW   39   /* map switches done                                        */
#define R_MAP_RST  40   /* map resets (sides disagreed -> back to empty map)        */
#define R_MAP_A_LO 41   /* blacklist A, bit i = RF channel i+2  (bits 0..31)        */
#define R_MAP_A_HI 42   /*                                      (bits 32..38)       */
#define R_MAP_B_LO 43   /* blacklist B, bit i = RF channel i+42 (bits 0..31)        */
#define R_MAP_B_HI 44   /*                                      (bits 32..38)       */
#define R_MAP_PEND 45   /* RX: proposed version waiting / TX: version being announced */
#define R_T_MAPS   46   /* TX: map proposals received                               */
/* R3b automatic TX power (TX) */
#define R_PC_REQ   47   /* power the controller asks for, ddBm ([19] = what RAIL set) */
#define R_PC_UPS   48   /* jumps to full power (weak signal, low LQ, telemetry lost) */
#define R_PC_DOWNS 49   /* 2 dB steps down                                          */
#define R_PC_RSSI  50   /* RSSI at the RX the controller last acted on, dBm         */
/* R3c alarms (TX) */
#define R_ALARM    51   /* 0 ok, 1 warning (weak link), 2 critical (no telemetry / RX failsafe) */
/* R4 listen-before-talk (both roles) */
#define R_LBT_BUSY 52   /* packets skipped because the channel was busy          */
#define R_SBUS     54   /* RX: SBUS frames sent on PA03                         */
#define R_LBT_TL   53   /* busy threshold used for the last transmission, dBm   */
#define R_VBAT     55   /* RX battery, mV (RX: measured / TX: from telemetry), 0 = no sensor */
#define R_VB_ALM   56   /* TX: RX battery alarm 0/1 low/2 critical / RX: 0 no sensor, 1 probing, 2 measuring */
#endif
